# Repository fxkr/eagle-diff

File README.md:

# eagle-diff

Show differences between Cadsoft Eagle PCB layouts

Author: Felix Kaiser <felix.kaiser@fxkr.net>  
License: revised BSD (see LICENSE)  
Version: 0.1.0  

## Usage

```
eagle-diff [-h] [-V] [-d DPI] [--eagle EAGLE] file1 file2 [output]

Show differences between Cadsoft Eagle files

positional arguments:
  file1              'old' version of the .brd file
  file2              'new' version of the .brd file
  output             output directory (will be created; default: eagle_diff)

optional arguments:
  -h, --help         show this help message and exit
  -V, --version      show program's version number and exit
  -d DPI, --dpi DPI  resolution of the generated images (default: 600)
  --eagle EAGLE      eagle binary to use (default: eagle)
```

## Samples

Here are some low-resolution sample images of the bottom side of a simple PCB.

Individual images of the "new" version of the board:

Diffs, without and with background image:

As usual, additions are green and deletions are red. You can easily see that some
traces and vias have been moved and the remaining traces have been made thicker.

## Dependencies

- Python Imaging Library (http://www.pythonware.com/products/pil/)
- CadSoft EAGLE (www.cadsoft.de)

## Caveats

- No cropping to dimension layer rectangle.
- The old and new images are aligned based on the boundary box around everything
  on the dimension layer. If the size of that boundary box changes, the layouts
  will probably not be aligned correctly.

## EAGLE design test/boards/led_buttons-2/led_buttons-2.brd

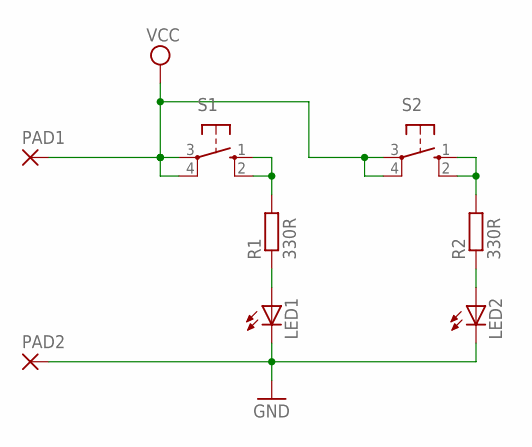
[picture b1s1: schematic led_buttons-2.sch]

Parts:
LED1, LED2: LEDCHIP-LED0603; CHIP-LED0603
PAD1, PAD2: SMD5; SMD2,54-5,08
R1, R2: 330R; R0603
S1, S2: 10-XX; B3F-10XX

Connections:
GND: LED1.C, LED2.C, PAD2.1
unnamed: R1.2, S1.1 (S), S1.2 (S1)
unnamed: LED1.A, R1.1
unnamed: R2.2, S2.1 (S), S2.2 (S1)
unnamed: LED2.A, R2.1
VCC: PAD1.1, S1.3, S1.4 (P1), S2.3, S2.4 (P1)

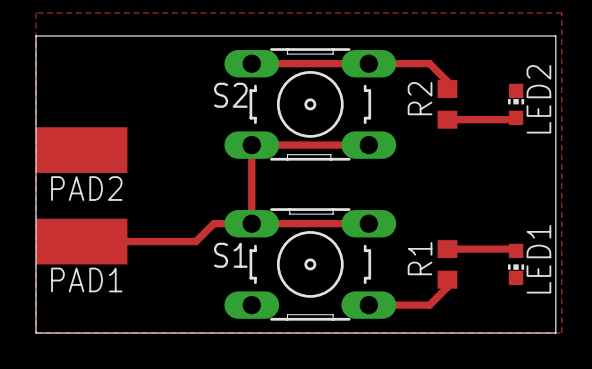
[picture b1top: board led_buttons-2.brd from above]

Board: 2 copper layers, 28.9 x 16.5 mm, 8 parts (0 on the bottom side), 6 nets.

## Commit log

2013-10-04 Add .gitignore
2013-10-06 Import eagle-diff script
    Behaviour currently mostly hardcorded;
    will have to be made more flexible.
2013-10-06 Add --dpi parameter
2013-10-06 Refactoring
2013-10-06 Add "copper-bottom" view
2013-10-06 Add "default" view
2013-10-06 Rewrite diff rendering; add desaturated bg image
2013-10-06 Sort imports
2013-10-07 Also generate diffs without background
2013-10-07 Add --eagle param to select eagle binary to use
2013-10-07 Validate --dpi parameter
    Eagle requires it to be in [1, 2400].
2013-10-07 Make output directory argument optional
2013-10-07 Add help text
2013-10-07 Change import style
    More sane and also necessary for Pillow compatibility.
    (PIL is heavily outdated; Pillow, a fork, is the new PIL.)
2013-10-07 Add help texts to options
2013-10-07 Add README, LICENSE and manpage
2013-10-07 Add linebreak to README
2013-10-07 Add sample images to README
2013-10-07 Add PKGBUILD and setup.py
2013-10-07 Set version to 0.1.0
2014-09-22 Run undo command after ratsnest
    That way Eagle won't ask about saving changes when quitting.
2014-09-22 Align files based on dimension layer
2014-09-22 Add views for internal layers
    For these, we change the filling style to solid, because otherwise
    the fills don't always match exactly, leading to hilights where there
    are no changes.
2015-03-01 Fix #14: Unknown layers popup in Eagle
2015-03-03 Fix #16: always use black palette
    Thanks to @PhracturedBlue!
2015-03-03 Fix #17: Error msg when "eagle" binary isnt found
2015-03-11 Better error msg when dimension layer is empty
2015-03-12 Fix #18: copper-top/bot.diff_bg had filled bg
2015-10-20 allow forcing output directory
    Sometimes you just want to re-run, without manually deleting the
    directory first, or explicitly providing a new directory. Add a
    -f,--force option that uses an existing directory.
2015-10-20 Support visual diff of schematic files as well.
    Limitations:
    * Assumes all sheets to be the same size.
    * default DPI settings makes quite large images.
2015-10-21 Example git diff wrapper script
    Demonstrates opening up the system default app with multiple files.
    (xdg-open can only open one file at a time) This also lets you do git
    diffs directly, rather than having to use "git difftool -t eagle" or
    similar workarounds.
2015-10-22 eagle-diff-git: remove trailing whitespace
2015-10-22 eagle-diff-git: add comment
2015-10-22 eagle-diff-git: quote all variables
2015-10-22 eagle-diff-git: set -e
2015-10-22 eagle-diff-git: use temporary directory
2015-10-22 eagle-diff-git: use /bin/bash
    Who knows if I've used a bashism?
2015-10-22 eagle-diff-git: add TODO comments
2015-10-22 eagle-diff-git: quieten grep
2015-10-22 eagle-diff-git: allow user to override DPI
2015-10-22 eagle-diff-git: set default DPI
    So it doesn't fail if the filename doesn't end with .brd or .sch.
    It'd probably be better to move this into eagle-diff,
    where we detect the type of the file by examining its contents
    already anyway and so don't have to rely on the filenames being correct.
2015-10-22 eagle-diff-git: actually match '.' (dot) with grep
2018-02-03 Add test data for repeatable test
2018-02-03 Add exporting names and values diff
2018-04-06 Fix for issue 29
